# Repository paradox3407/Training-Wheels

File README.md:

# Training Wheels

ESP32 based two wheeled self balancing robot with a custom PCB, chassis, firmware! Want to learn how to implement a control loop or just want to build a cool robot? Training Wheels is for you! 

## Features

- PID Control Algorithm 
- IMU Calibration Program
- Convenient Troubleshooting:
  - Headers for swapping ICs: ESP32, MPU6050, A4988 Stepper Motor Driver Breakout
  - LED indicators for VDD and GPIO 
- Nema 17 Stepper Motors
- Power Switch

## Overview

This project was made for [Hackclub's](https://hackclub.com/programs) Fallout Program. I built this because I wanted to make a project that encompasses mechanical, electrical, and software engineering, all while exploring PID control through implementing the prototyping process and good design practices. Through the ~70 hours spent on this project I learned the value of documentation, time management, how to select components, read datasheets, how to CAD using assemblies and designing in context, schematic, part layout and wiring good practices, version control, PID control theory and tuning, and so much more! (Might have gotten a caffeine addiction too...)

## Gallery 

<details>
  <summary> Click to expand </summary>
  <br>

  ### Chassis / Assembly
  *Designed in Onshape* 
  
  Source Files found [here](https://cad.onshape.com/documents/563a6cb8d162cb6cd823a1f9/w/2660c435afac39828b2200f7/e/e81ee193bff4145dfd9a22a6?renderMode=0&uiState=6a32417e83808aa5af5cc75c)

  ### PCB 
  *Designed in KiCad*

  #### Schematic

  #### Layout

</details>

## Firmware (Setup + Tuning)

*Written in C++ using VSCode + [PlatformIO](https://platformio.org/)*

### How to Build & Flash
1. Clone this repository.
2. Open the `Firmware/Self-Balancing-Robot` folder in VS Code with PlatformIO installed.
3. Connect your ESP32 via USB.
4. Click the PlatformIO **Upload** button 

The IMU must be calibrated before running the main code. Run the [calibration program](./Firmware/Self-Balancing-Robot/src/calibration/MPU_calibration.cpp) while the robot is upright and in a stable position. 

### How to Tune

Then run the [main code](./Firmware/Self-Balancing-Robot/src/robot_main/main.cpp). To get the robot to balance, modify these values:

```cpp
const float desiredOutput = 0; // desired angle 
const float Kp = 0; 
const float Ki = 0;
const float Kd = 0; 
```
Tune these values in the following order: 
`desiredOutput` is used for setting the offset for the balance point of the robot. 

`Kp` is the proportional gain, and it will be doing most of the "work": increase by powers of two until the robot oscillates, then decrease by 20%.

`Kd` is the derivative gain, and it addresses oscillations. Increase by small increments, starting roughly at 0.05, until the robot stops oscillating. 

`Ki` is the integral gain, which address drift. By this point the robot should be balancing but if it glides forward or backwards, increase this value, also starting small. Note that `Ki` might not always need to be modified. 

The key to tuning is patience! Only modify one value at a time, and increment in small values. 

## Zine

*Designed in Figma*

## Acknowledgements

Designed by Sara C / paradox3407

**Special thanks** to my robotics mentors for reviewing my designs and giving me much needed feedback! + Jennifer for creating inspiration/reference sketches for the chassis + Ellie for teaching me the basics of calculus at flex when I was trying to learn the math behind PID + Hackclub and Fallout!

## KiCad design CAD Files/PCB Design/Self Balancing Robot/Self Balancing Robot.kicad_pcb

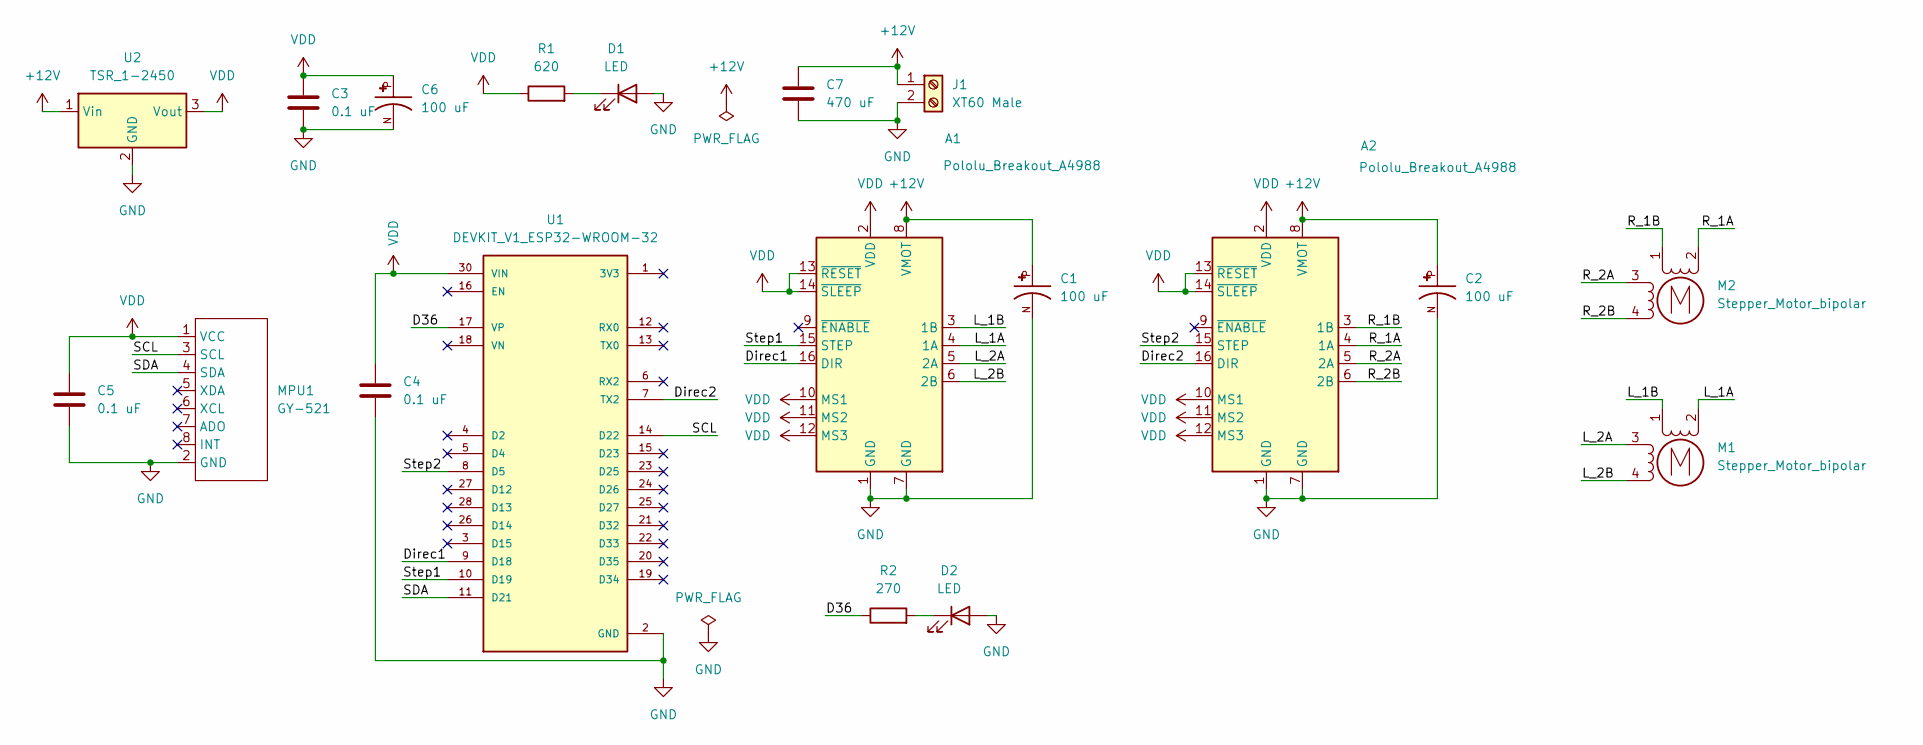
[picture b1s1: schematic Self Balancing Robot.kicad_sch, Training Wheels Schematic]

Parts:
A1, A2: Pololu_Breakout_A4988; Pololu_Breakout-16_15.2x20.3mm
C1, C2, C6: 100 uF; CP_Radial_D6.3mm_P2.50mm; PARTREV 20-DEC-19
C3, C4, C5: 0.1 uF; C_0805_2012Metric_Pad1.18x1.45mm_HandSolder
C7: 470 uF; CP_Radial_D10.0mm_P5.00mm
D1, D2: LED; SMD LED 1206
J1: XT60 Male; AMASS_XT60-M_1x02_P7.20mm_Vertical
M1, M2: Stepper_Motor_bipolar; JST_XH_S4B-XH-A_1x04_P2.50mm_Horizontal
MPU1: GY-521; MODULE_GY-521
R1: 620; R_1206_3216Metric_Pad1.30x1.75mm_HandSolder
R2: 270; R_1206_3216Metric_Pad1.30x1.75mm_HandSolder
U1: DEVKIT_V1_ESP32-WROOM-32; MODULE_DEVKIT_V1_ESP32-WROOM-32
U2: TSR_1-2450; Converter_DCDC_TRACO_TSR-1_THT

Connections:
+12V: A1.8 (VMOT), A2.8 (VMOT), C1.P, C2.P, C7.1, J1.1, U2.1 (Vin)
/D36: R2.1, U1.17 (VP)
/Direc1: A1.16 (DIR), U1.9 (D18)
/Direc2: A2.16 (DIR), U1.7 (TX2)
/L_1A: A1.4 (1A), M1.2 (-)
/L_1B: A1.3 (1B), M1.1
/L_2A: A1.5 (2A), M1.3
/L_2B: A1.6 (2B), M1.4
/R_1A: A2.4 (1A), M2.2 (-)
/R_1B: A2.3 (1B), M2.1
/R_2A: A2.5 (2A), M2.3
/R_2B: A2.6 (2B), M2.4
/SCL: MPU1.3 (SCL), U1.14 (D22)
/SDA: MPU1.4 (SDA), U1.11 (D21)
/Step1: A1.15 (STEP), U1.10 (D19)
/Step2: A2.15 (STEP), U1.8 (D5)
GND: A1.1 (GND), A1.7 (GND), A2.1 (GND), A2.7 (GND), C1.N, C2.N, C3.2, C4.2, C5.2, C6.N, C7.2, D1.2 (A), D2.2 (A), J1.2, MPU1.2 (GND), U1.2 (GND), U1.29 (GND), U2.2 (GND)
unnamed: D1.1 (K), R1.2
unnamed: D2.1 (K), R2.2
VDD: A1.2 (VDD), A1.10 (MS1), A1.11 (MS2), A1.12 (MS3), A1.13 (~RESET), A1.14 (~SLEEP), A2.2 (VDD), A2.10 (MS1), A2.11 (MS2), A2.12 (MS3), A2.13 (~RESET), A2.14 (~SLEEP), C3.1, C4.1, C5.1, C6.P, MPU1.1 (VCC), R1.1, U1.30 (VIN), U2.3 (Vout)

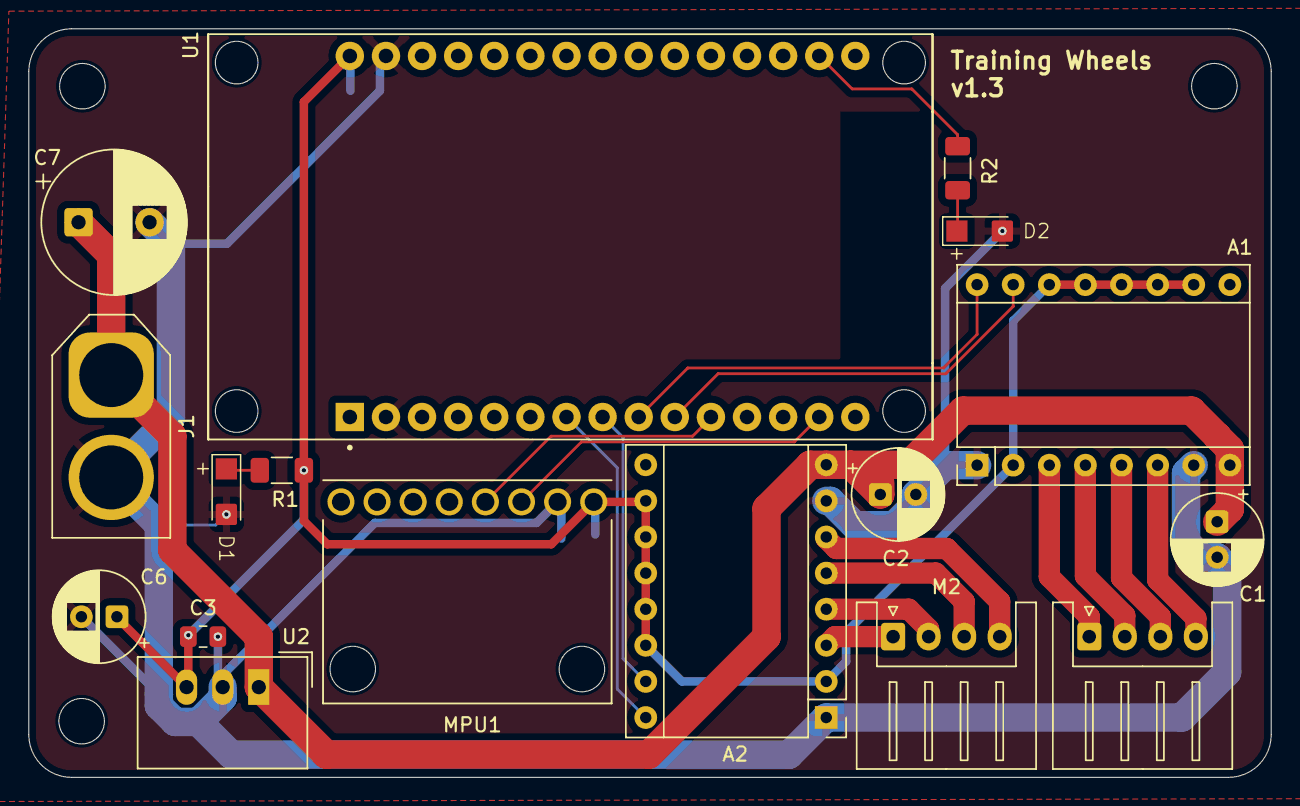
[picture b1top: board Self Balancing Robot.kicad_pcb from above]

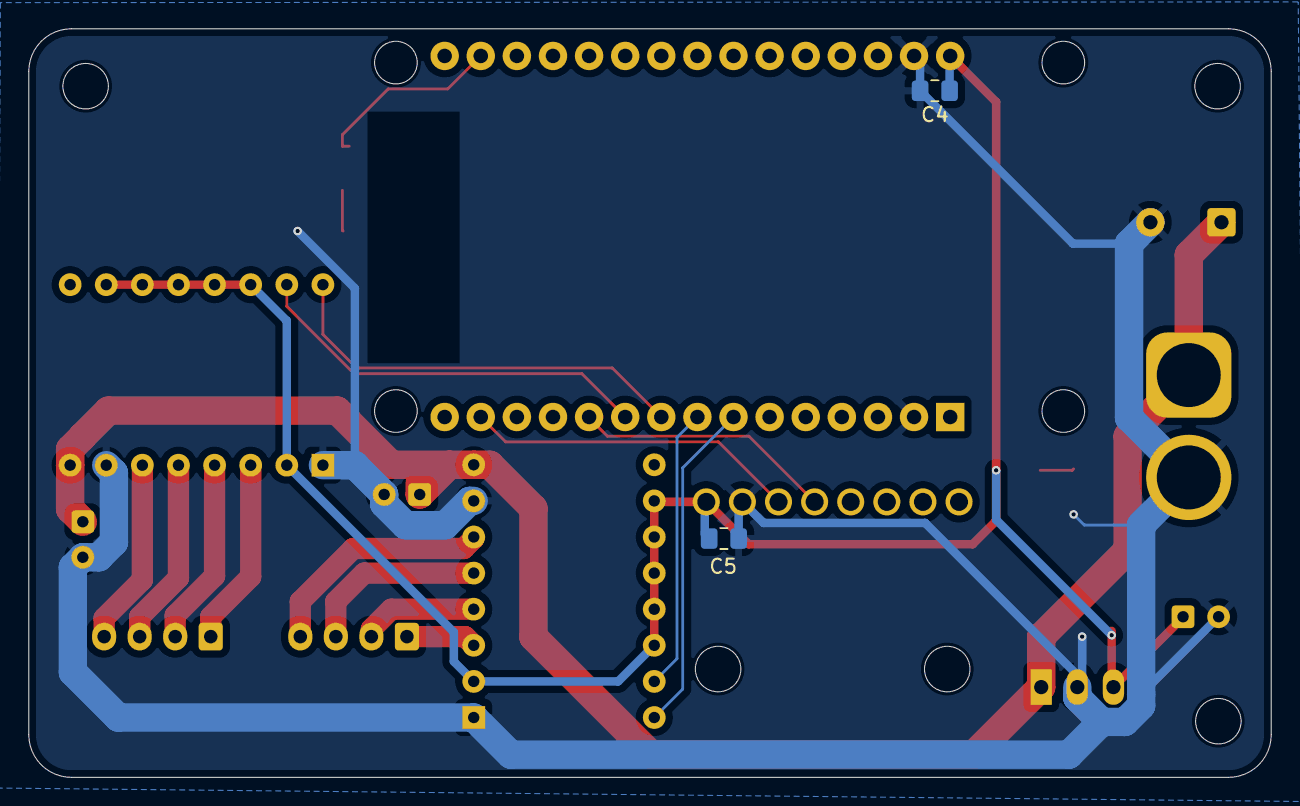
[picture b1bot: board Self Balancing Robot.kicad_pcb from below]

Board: 2 copper layers, 87.4 x 52.7 mm, 19 parts (2 on the bottom side), 20 nets.

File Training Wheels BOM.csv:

Item,Description,Quantity,Unit Price ($),Total Price ($),URL,Running Total ($ with Tax)
Pololu_Breakout_A4988,Motor Driver,2,8.95,17.9,https://www.pololu.com/product/1182,19.2
ECA1HM101,Capacitor,2,$0.45,$0.90,https://www.digikey.com/en/products/detail/panasonic-industr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,$20.75
Red SMD LED,Indicator LEDs,2,$0.15,$0.30,https://www.sparkfun.com/red-led-surface-mount-1206.html,$21.27
Screw_Terminal_01x02,Power Terminal,1,$1.54,$1.54,https://www.mouser.com/ProductDetail/Altech/MV-152?qs=sGAEpi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,$23.93
Wire Ferrules,For Power wires,1,13.18,13.18,https://www.aliexpress.com/i/2251832854626098.html?gatewayAd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,$46.67
Stepper_Motor_bipolar,Motors,2,$9.13,$18.26,https://www.omc-stepperonline.com/nema-17-bipolar-45ncm-63-7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,$55.43
GY-521,MPU Breakout Board,1,$5.94,$5.94,https://www.aliexpress.us/item/3256809115197759.html?src=goo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,$65.68
620 Ohm Resistor,Resistor,1,0.1,0.1,https://www.mouser.com/ProductDetail/YAGEO/AC1206FR-7W620RL?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,$65.85
270 Ohm Resistor,Resistor,1,$0.19,$0.19,https://www.mouser.com/ProductDetail/Vishay/RCA1206270RJNEA?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,$66.18
DEVKIT_V1_ESP32-WROOM-32 TYPE-C 30PIN,Microcontroller,1,$12.24,$12.24,https://www.aliexpress.us/item/3256809051361454.html?src=goo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,$87.29
TSR_1-2450,DC DC CONVERTER 5V 5W,1,$6.16,$6.16,https://www.digikey.com/en/products/detail/traco-power/TSR-1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,$97.92
Bismuth Solder Paste,For SMD Soldering ,1,16.99,16.99,https://www.amazon.com/Solder-Paste-Soldering-Electronic-Rem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,$127.23
LED Rocker Swith,Power Switch,1,$5.73,$5.73,https://www.aliexpress.us/item/3256810220221486.html?algo_ex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,$137.11
18650 2500mAh 20A Battery,Battery,3,$4.99,$14.97,https://www.18650batterystore.com/products/samsung-25r-18650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,$162.93
18650 Battery Holder,Battery Holder,1,$2.40,$2.40,https://www.digikey.com/en/products/detail/dfrobot/FIT0539/8549502,$167.07
S4B-EH,Motor connector,2,$0.16,$0.32,https://www.digikey.com/en/products/detail/jst-sales-america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,$167.62
"2.54mm 0.1"" 15-pin Female Header",ESP32 Header,2,$1.63,$3.26,https://www.electromaker.io/shop/product/254mm-01-15-pin-fem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,$173.24
WR-PHD 2.54 MM SOCKET HEADER; 8,Motor Driver Header,5,$0.40,$2.00,https://www.digikey.com/en/products/detail/w-rth-elektronik/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,$176.69
M3-0.5x12 Class 12.9 Alloy Flat Socket Head Cap Screws ,Battery Mounting Screws ,6,0.18,1.08,https://boltsandnuts.com/products/m3-0-5x12-class-12-9-alloy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,$178.55
M3 x 6mm Full Thread Socket Cap Head Screws ,PCB mounting Screws,11,0.26,2.86,https://accu-components.com/us/metric-cap-head-screws/3817-S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,$183.48
85mm Mecanum Wheel High Grip Rubber Tires ,Wheel,2,6.73,13.46,https://www.aliexpress.us/item/3256804851566721.html?gateway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,$206.70
6mm coupling,Wheel Coupling,2,6.73,13.46,https://www.aliexpress.us/item/3256804851566721.html?gateway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,$229.92
PCB,PCB ,1,$4.00,$4.00,https://cart.jlcpcb.com/quote,$236.82
,,,,,,
,,,,,Total: ,$236.82

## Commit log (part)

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2026-06-09 Initial commit: Fresh start
2026-06-09 Reformatting firmware files in git
2026-06-09 Started porting main code (Arduino nano to ESP32)
2026-06-09 Delete Resources directory
    Cleaning up repo
2026-06-09 Delete Documentation/Pictures directory
    Clean up repo
2026-06-09 Add gitignore for documentation and resoruces files
2026-06-09 Revert "Delete .vscode directory"
    This reverts commit 894657d652b7f5cf0018379baba0b6b4bcc78276.
2026-06-09 Revert "Delete Documentation/Pictures directory"
    This reverts commit 224c5d74ac6d80b425e2d51eaef2f140f06926cc.
2026-06-09 Reverted accidently deleted files and fixed gitignore
2026-06-09 Fixed gitignore heirarchy/added new gitignore
2026-06-09 Ignore Pictures folder
2026-06-09 Fixed .gitignore and deleted cached documentation folder
2026-06-09 final gitignore fix
2026-06-10 configure gitignore for new test file
2026-06-10 addcorrect baud rate to platformio setup
2026-06-10 Restructed project setup for multiple environments/builds
2026-06-10 Added MPU calibration program
2026-06-11 Ported code to stepper motors and ESP32
2026-06-11 Fix incorrect gyro offset print statements in MPU calibration
2026-06-11 Refactor project structure: update .gitignore, remove obsolete files
2026-06-11 Update README to remove testing note
    Remove testing note from README
2026-06-11 Created PCB schematic
2026-06-11 Resolved pin errors
2026-06-11 Add placeholder for future updates in README
2026-06-11 VDD power flag fix
2026-06-11 Added battery terminal, updated capacitor symbol, and assigned footprints.
2026-06-12 Fix schematic by adding screw terminal for battery, added indicator LEDS (and resistors), made custom footprints for capacitors, LEDS, configured libraries, made gitignore for PCB design folder
2026-06-12 Apply updated .gitignore and untrack cached files
2026-06-12 Added MPU (GY-521) footprint
2026-06-13 Positioned components on PCB, drew traces, assigned step files
2026-06-13 Add 3d models
2026-06-14 Fixed minor labeling and wiring aesthetics
2026-06-14 Generated gerber files
2026-06-14 Update .gitignore to exclude additional KiCAD temporary files
2026-06-15 Added Overview, Features, Gallery, Firmware, Acknowledgements sections
2026-06-15 Made gallery collapsible
2026-06-16 Added link to source files
2026-06-16 Add CAD settings for Chassis V2 zip file to .gitignore
2026-06-16 Add Bill of Materials (BOM)
2026-06-16 Add step files
2026-06-16 Stop tracking Chassis v2 zip file
2026-06-17 Update Bill of Materials (BOM) with new components and remove obsolete entries
2026-06-17 Update 3d models of ESP32
2026-06-17 Add drill files
2026-06-17 Update with new photos and zine
2026-06-17 Update with fixed PCB photo
2026-06-17 update with correct Chassis source file
